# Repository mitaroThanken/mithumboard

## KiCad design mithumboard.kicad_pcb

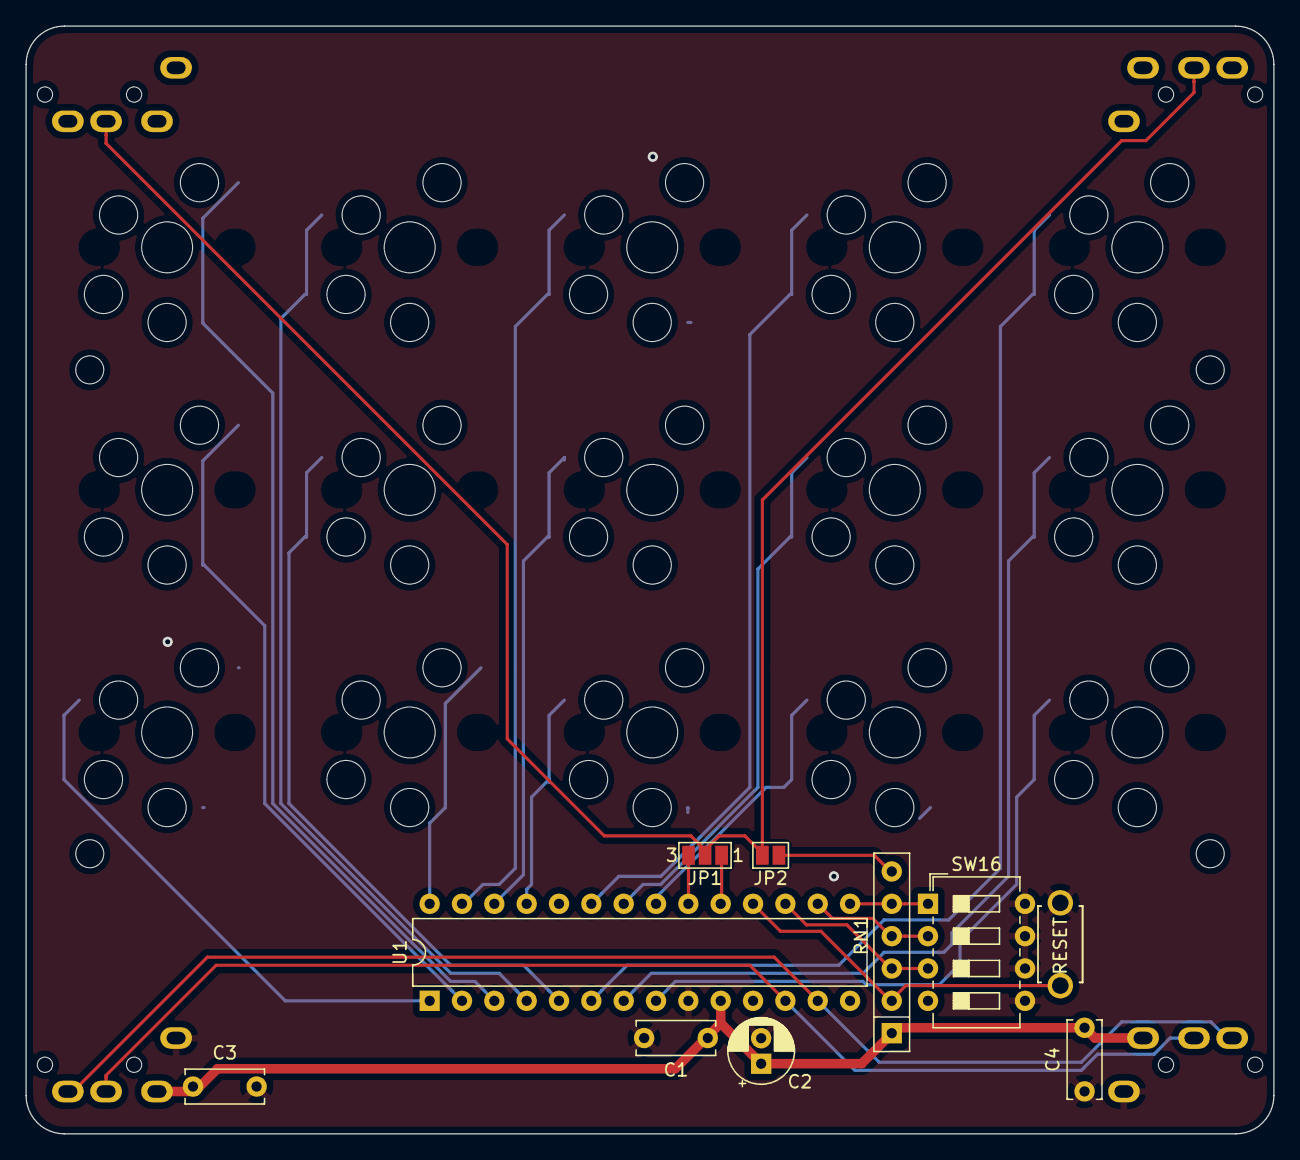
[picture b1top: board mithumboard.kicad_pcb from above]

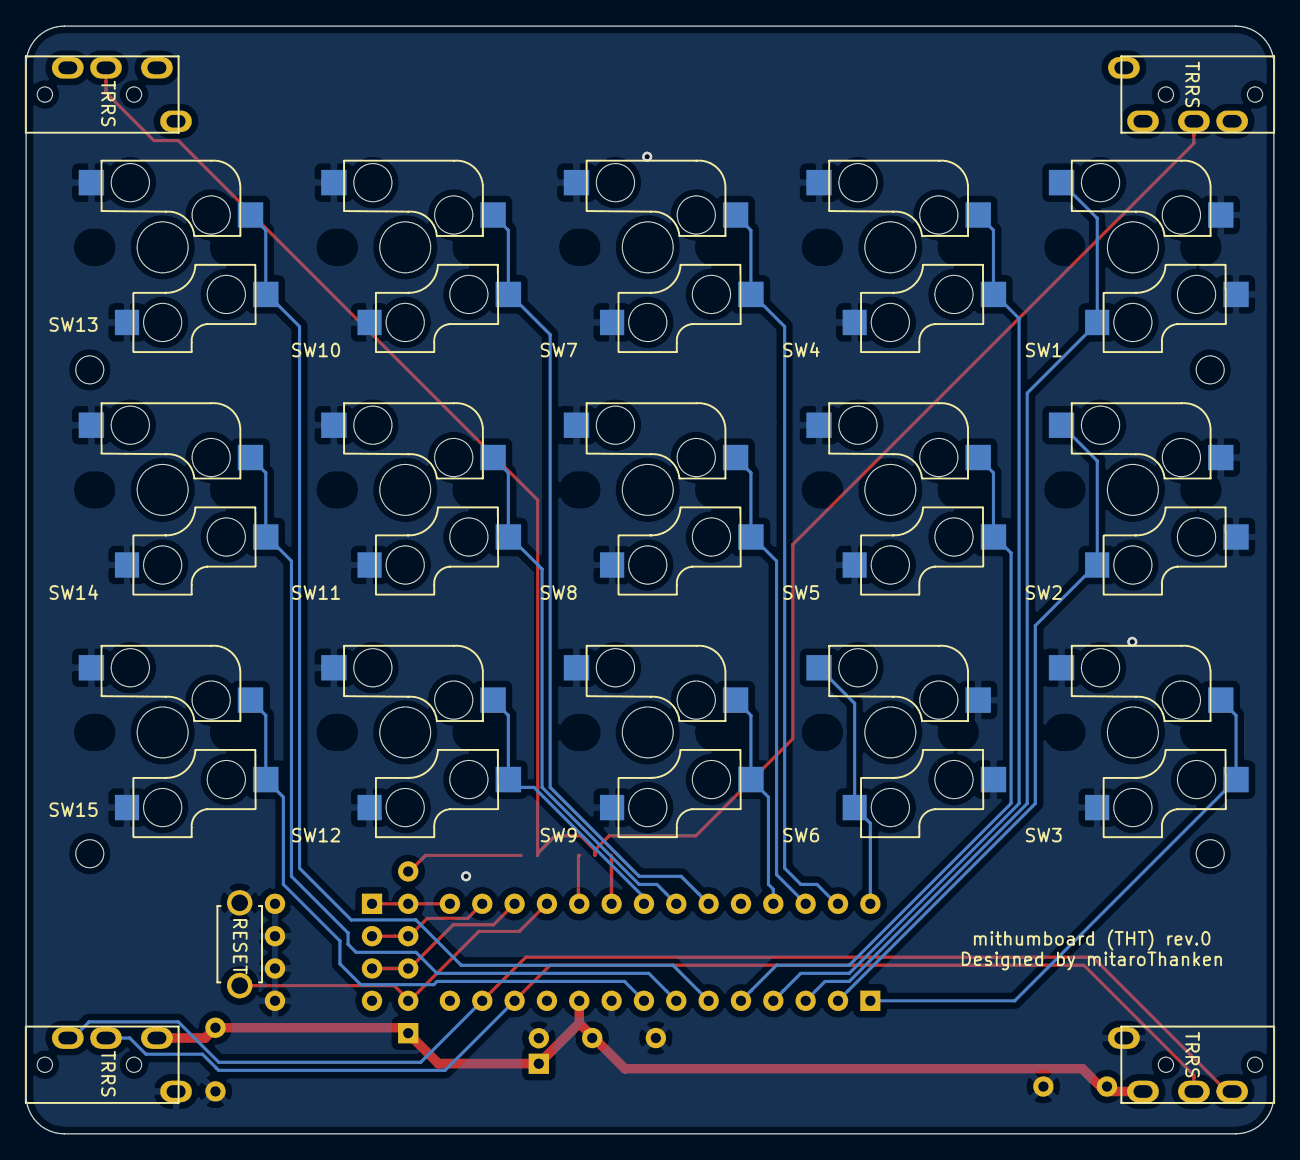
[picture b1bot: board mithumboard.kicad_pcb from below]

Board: 2 copper layers, 98.0 x 87.0 mm, 33 parts (8 on the bottom side), 27 nets.

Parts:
C1: 0.1u; C_Disc_D6.0mm_W2.5mm_P5.00mm
C2: 47u/16V; CP_Radial_D5.0mm_P2.00mm
C3, C4: 1u; C_Disc_D6.0mm_W2.5mm_P5.00mm
H1, H2, H3, H4: MountingHole; MountingHole_2.2mm_M2
J1, J2, J3, J4: MJ-4PP-9; MJ-4PP-9_1side
JP1: Jumper_3_Open; SolderJumper-3_P1.3mm_Open_Pad1.0x1.5mm_NumberLabels
JP2: Jumper_2_Open; SolderJumper-2_P1.3mm_Open_Pad1.0x1.5mm
RN1: 10k; R_Array_SIP6
SW1, SW2, SW3, SW4, SW5, SW6, SW7, SW8, SW9, SW10, SW11, SW12, SW13, SW14, SW15: SW_Push; CherryMX_Choc_Hotswap_1side
SW16: SW_DIP_x04; SW_DIP_SPSTx04_Slide_6.7x11.72mm_W7.62mm_P2.54mm_LowProfile
SW17: SW_Push; ResetSW
U1: MCP23017_SP; DIP-28_W7.62mm

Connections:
A0: RN1.5, SW16.1, U1.15
A1: RN1.4, SW16.2, U1.16
A2: RN1.3, SW16.3, U1.17
GND: C1.2, C2.2, C3.1, C4.1, J1.A, J2.A, SW1.1, SW2.1, SW3.2, SW4.2, SW5.2, SW6.1, SW7.2, SW8.2, SW9.2, SW10.2, SW11.2, SW12.2, SW13.2, SW14.2, SW15.2, SW16.5, SW16.6, SW16.7, SW16.8, SW17.2, U1.9
INT: J3.C, J4.C, JP1.2, JP2.2
INTA: JP1.3, U1.20
INTB: JP1.1, U1.19
unnamed: JP2.1, RN1.6
R1C1: SW1.2, U1.3
R1C2: SW4.1, U1.4
R1C3: SW7.1, U1.27
R1C4: SW10.1, U1.23
R1C5: SW13.1, U1.6
R2C1: SW2.2, U1.2
R2C2: SW5.1, U1.5
R2C3: SW8.1, U1.26
R2C4: SW11.1, U1.22
R2C5: SW14.1, U1.7
R3C1: SW3.1, U1.1
R3C2: SW6.2, U1.28
R3C3: SW9.1, U1.25
R3C4: SW12.1, U1.21
R3C5: SW15.1, U1.8
RESET: RN1.2, SW17.1, U1.18
SCL: J1.C, J2.C, U1.12
SDA: J1.B, J2.B, U1.13
VCC: C1.1, C2.1, C3.2, C4.2, J1.D, J2.D, RN1.1, U1.10

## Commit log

2019-03-31 テンプレートから作成
2019-03-31 ライブラリを更新
2019-03-31 README をとりあえず更新。WIP。
2019-04-06 foostan/kbd をフォークし、MJ-4PP-9 の各ピンをパッシブに変更
2019-04-06 modulo-ergo42 を参考に、構成要素を置いてみる
2019-04-06 フットプリントと関連付け
2019-04-06 キースイッチをCherryMXのソケットのみに変更
2019-04-06 基板レイアウト開始。一部パーツ変更。
2019-04-06 キースイッチのピン割り当て見直し
2019-04-06 さらに配線見直し。
    配線は完了？
2019-04-06 キースイッチのソケット、片面のみのフットプリントを用意。
2019-04-06 全部線引き終わり
    ただし基板を180度回転させたので、キースイッチの行列のラベルを張りなおす必要あり。
2019-04-06 ソケットのフットプリントを片面のみにし、再配線
2019-04-07 PJ-320D のピンアサインを修正して、配線・配置を再整頓
2019-04-07 スペーサー用の穴をあけるのを忘れてた
2019-04-08 キースイッチの向きを統一
    するためにジャックの向きを変更し、キースイッチ群の外に移動。
    ……上の隙間はなくしたかったんだけれど、あきらめるか……
2019-04-08 MJ-4PP-9 の修正を再取り込み
2019-04-09 再配置完了？
    穴あけがまだ。
2019-04-09 不要になったピラーを除去
2019-04-10 穴開けてみた
2019-04-10 MCP23017 に変更。配線開始。
    キースイッチ以外は一応引けた。はず。
2019-04-10 キースイッチまで配線終わり
2019-04-11 MCP23017 に置き換えて線を引きなおし
    これであってるのかさっぱりわからん。
2019-04-12 INT 周りを修正
    基本、INTA だけを使用。
    いざというときに INTB も使えるようにしておく。
    また、プルアップの抵抗も使わない予定だけれど、念のためパターンは置いておくことにする。
2019-04-12 キャッシュを除外対象にする
2019-04-13 フットプリント全更新
2019-04-13 ジャンパのフットプリント変更
    エラーが出なきゃいいわけじゃなかった。
2019-04-13 キースイッチのフットプリント、穴広げてみた
2019-04-13 キースイッチのフットプリント、PCBマウント用穴を楕円に変更
    さすがに正円は大きすぎると思われたので。
2019-04-13 位置調整
2019-04-13 外枠切った
2019-04-16 TCA9555PWR に再度置き換え
2019-04-16 TCA9555PWR に置き換え、キースイッチ以外の配線をやり直し
    キースイッチへの再配線が残。
2019-04-16 一応配線完了
2019-04-16 プルアップ抵抗追加・コンデンサと抵抗を表層部品に変更
2019-04-16 配線見直し
2019-04-17 マウント用スルーホールをM2に変更
2019-04-17 層合わせターゲットを追加
2019-04-17 層合わせターゲット追加
2019-04-20 プルアップ抵抗とジャンパを変更
2019-04-21 部品をあらかた表面に移す
2019-04-21 DIP スイッチを SMD に変更
2019-04-21 縦方向 2mm ずつ長く
2019-04-21 リファレンスの被りを修正
2019-04-23 説明線がずれてた
2019-04-23 マウント穴の位置を調整・ガーバーデータ出力
2019-04-23 マウント穴調整・ガーバーデータ出力
